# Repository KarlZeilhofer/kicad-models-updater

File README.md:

kicad-models-updater
====================
Reload the 3D Models in a .kicad_pcb File from the Libraries
------------------------------------------------------------

You would like to use this script, if you have modified many of the 3D models
in your footprint libraries. Another use could be to get a verbose
health report regarding footprints and it's libraries.

It takes a `.kicad_pcb` file, laods the used footprints from the
libraries and modifies the entries for a 3D model in the PCB file
without modifying any other fields. A diff will show only
the intended modifications (great for git).

## Usage
run `kicad-models-updater` in your KiCad project directory, and the
rest should be done by the script.

If you have multiple config paths on your system (e.g. KiCad 4/5 in
parallel), you have to specify
one of them with `-c CONFIGPATH`.

### Help
```
usage: kicad-models-updater [-h] [-c CPATH] [-p PPATH] [-f PCBFILE]
                            [-o OUTPUTFILE] [--dryrun] [--version]

Gets paths for 3D models from the used footrints and updates it in the
.kicad_pcb file without changing any other properties in the layout.

optional arguments:
  -h, --help            show this help message and exit
  -c CPATH, --configpath CPATH
                        system wide config path, where kicad_comman and fp-
                        lib-table can be found. Default is
                        /home/karl/.config/kicad
  -p PPATH, --projectpath PPATH
                        path to kicad project, where .kicad_pcb and optional
                        fp-lib-table can be found. Default is the current
                        working directory
  -f PCBFILE, --pcbfile PCBFILE
                        .kicad_pcb file to be modified. Default is the
                        .kicad_pcb in the project path. The --projectpath is
                        overridden by a given --pcbfile
  -o OUTPUTFILE, --output OUTPUTFILE
                        .kicad_pcb file to write the modified PCB file to.
                        Default is the input file, see --pcbfile Use this
                        option, if you do not want to overwrite the original
                        file
  --dryrun              run through all steps, except writing the output file
  --version             show program's version number and exit

GitHub: https://github.com/KarlZeilhofer/kicad-models-updater
```

## Details
The footprint libraries are discoverd like they are discovered by KiCad
itself using `kicad_common`, global `fp-lib-table` and projcet's
`fp-lib-table`.
This leads to a very smooth user experience and best possible
integrity of the modifications.

Various warnings are reported, if something isn't as expected:
* missing kicad_common
* missing fp-lib-table
* missing footprint library
* missing 3D model file
* multiple model entries in library or PCB footprint

## Installation
The file `kicad-models-updater.py` should be made executable. I added a
symlink to `/usr/bin/kicad-models-updater` on my Linux system, so I
can easily call it from any project directory.

## Status
* tested on linux with python 3.5.2

## Limitations
* only for KiCad 4 and newer with fp-lib-table and .pretty libs
* path substitutions are applied only once (`KicadCommon.py`)

## License
GPL V3, (c) Karl Zeilhofer, www.team14.at

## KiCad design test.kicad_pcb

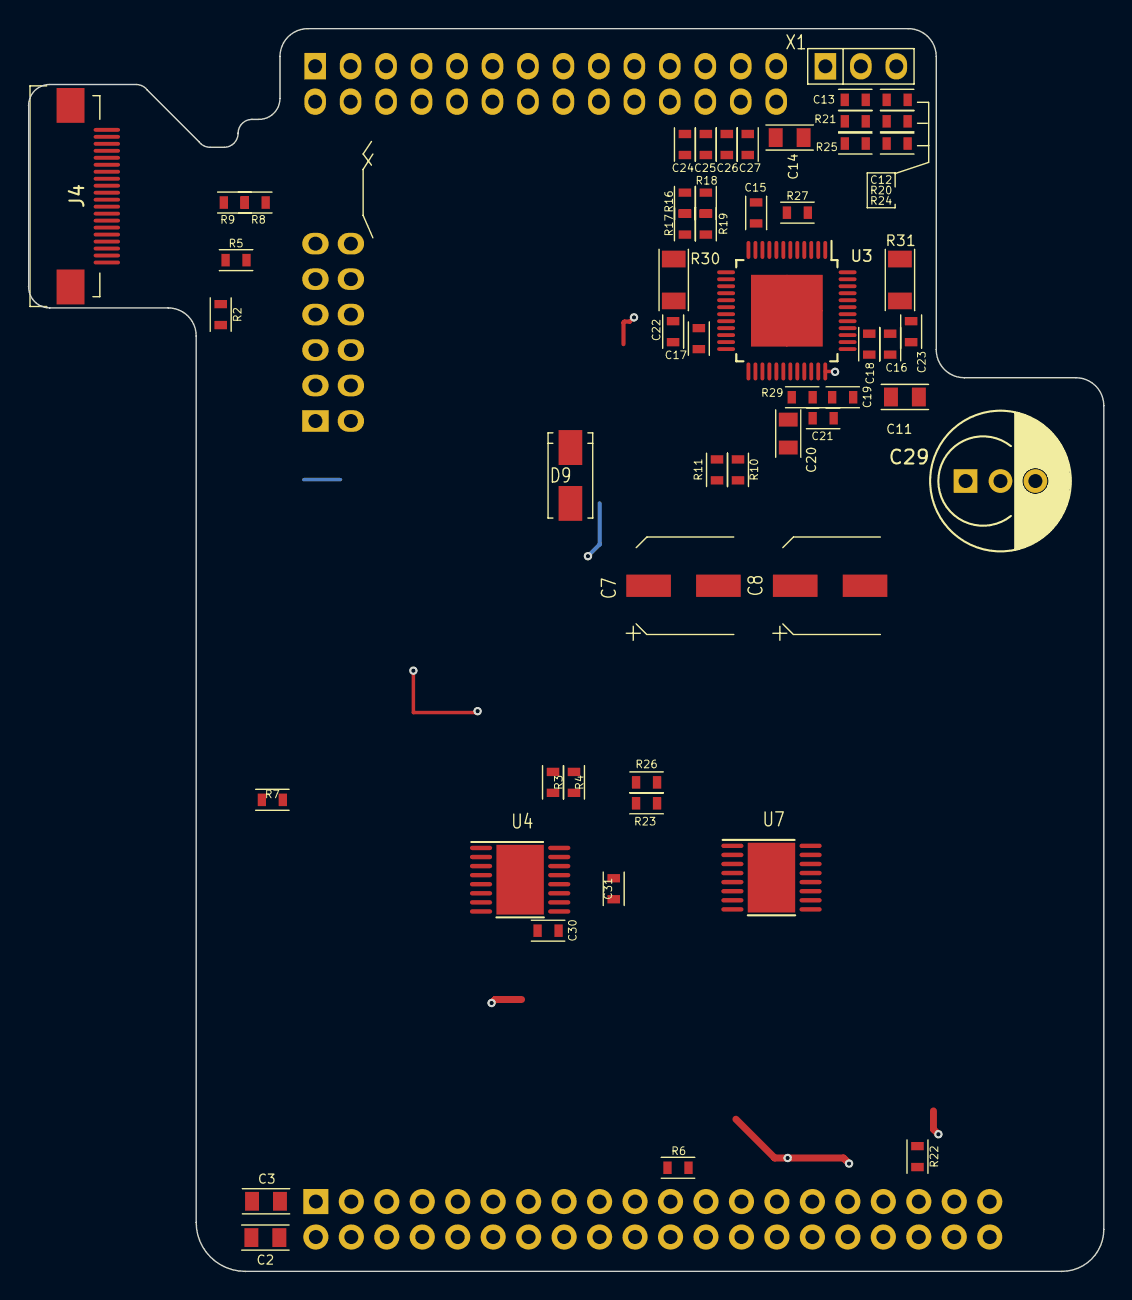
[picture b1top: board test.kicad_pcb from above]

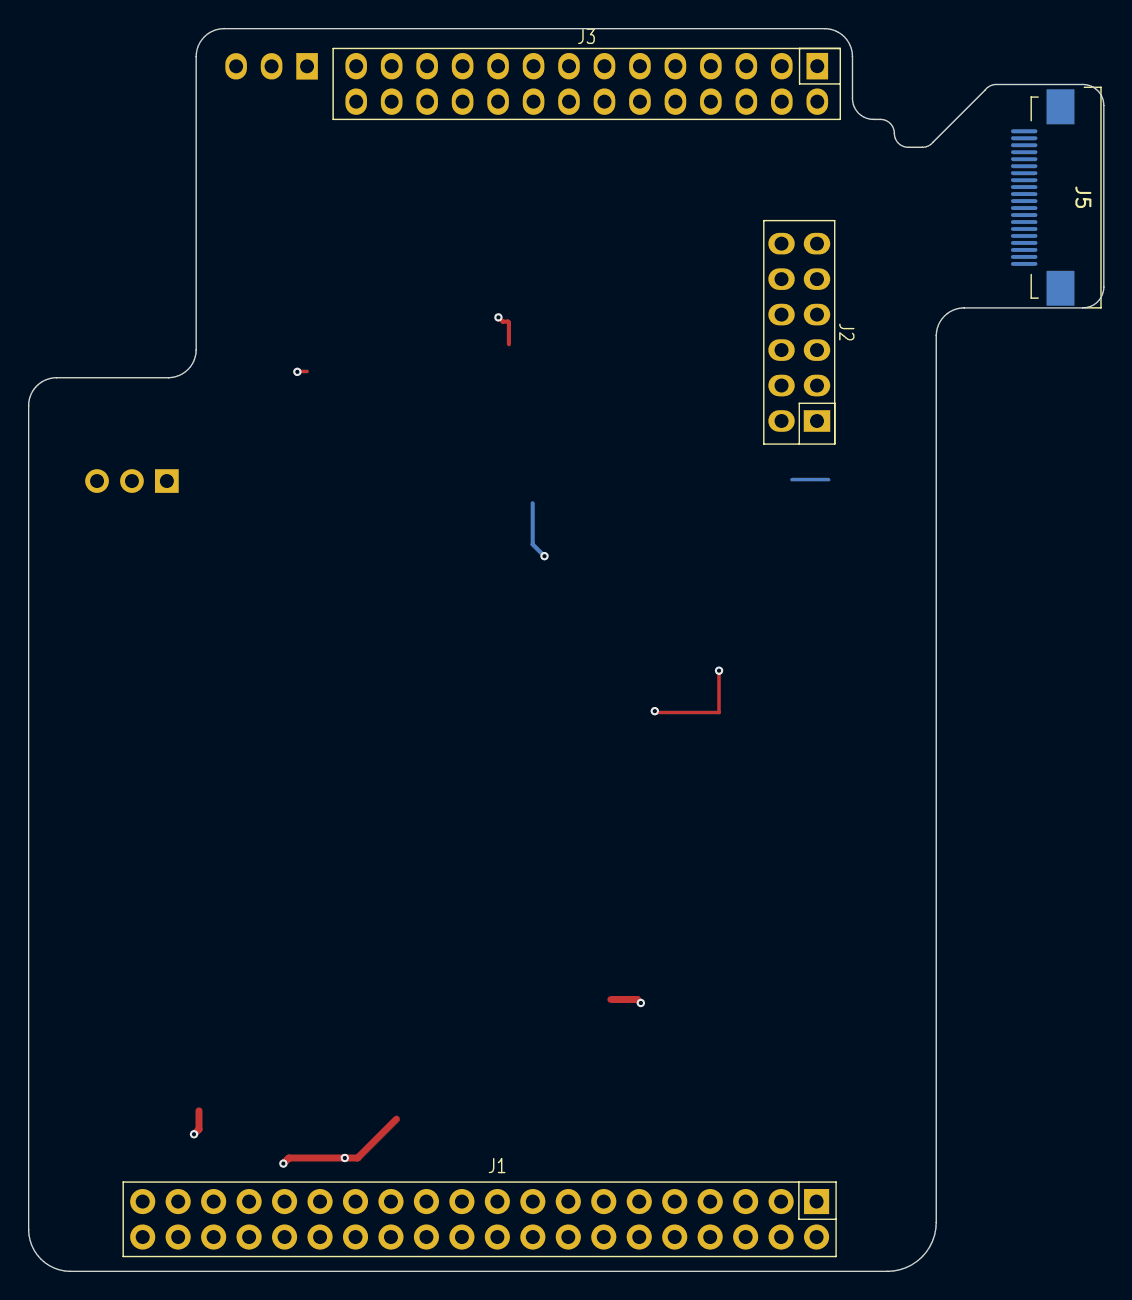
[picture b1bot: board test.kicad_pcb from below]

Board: 4 copper layers, 77.0 x 89.0 mm, 59 parts (4 on the bottom side), 45 nets.

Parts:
C2, C3: DNP; C2012m
C7, C8: C_pol; ELKO_D
C11, C14: 2u2/50V; C2012m
C12, C13: DNP; C1608m
C15, C18, C22, C23, C31: 100n; C1608m
C16, C17, C30: 100n/50V; C1608m
C19: 22n/50V; C1608m
C20: 4.7u; C2012m
C21: 470n; C1608m
C24, C25, C26, C27: 1n/ESD; C1608m
C29: C_pol; C_Radial_D10_D6.3
D9: SMAJ33CA; SMA
J1: Raspberry_Pi_2_3; Pin_Header_Straight_20x2_Female
J2: Buchse_02x06; Pin_Header_Straight_Female_2x6
J3: Buchse_02x14; Pin_Header_Straight_Female_2x14
J4, J5: ZIF0502DH; ZIF0520UH
R2, R3, R4, R5, R6, R7: 100R; R1608m
R8, R16, R19: 0R; R1608m
R9, R17, R18, R20, R21: DNP; R1608m
R10, R11, R22, R23, R26, R27: 470R; R1608m
R24, R25: 4k7; R1608m
R29: 3R3; R1608m
R30, R31: TBD; R3216m
U3: TMC5130-TA; TQFP-48-EP_7x7mm_Pitch0.5mm
U4, U7: DRV8816; HTSSOP-16_4.4x5mm_Pitch0.65mm_EP
X1: DNP; Pin_Header_Straight_1x3

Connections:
+3V3: C3.1, C15.1, J1.1, J1.17, J2.2, J4.1, J5.1, R9.1, R16.1, R18.1, R24.1, R25.1, U3.10
+5V: C2.1, J1.2, J1.4, J2.10, R8.1
/BLVDD: J4.17, J4.18, J5.17, J5.18, R8.2, R9.2
/CS_DISP_cab: J4.6, J5.6, R6.2
/GPIO34/VCP: C31.1, U4.14
/INT_DISP: J1.8, R2.1
/INT_DISP_cab: J4.7, J5.7, R2.2
/IO1: J3.10, U7.7
/IO2: J3.9, U7.10
/IO3: J3.8, U4.7
/IO4: J3.7, U4.10
/MISO: J1.21, R5.1, R27.1
/MISO_DISP: J4.4, J5.4, R5.2
/MOSI: J1.19, R4.1, R23.1
/MOSI_DISP: J4.5, J5.5, R4.2
/PD_DISP_cab: J4.8, J5.8, R7.2
/SCLK: J1.23, R3.1, R26.1
/SCLK_DISP: J4.3, J5.3, R3.2
/STP_A1: C26.2, J3.25, U3.46
/STP_A2: C27.1, J3.26, U3.42
/STP_B1: C24.2, J3.23, U3.15
/STP_B2: C25.1, J3.24, U3.19
/Stepperdriver/BRA: C23.1, R31.1, U3.44
/Stepperdriver/BRB: C22.1, R30.1, U3.17
/Stepperdriver/REFL_CON: C12.1, R20.2, X1.3
/Stepperdriver/REFR_CON: C13.1, R21.2, X1.2
/~CS_DISP: J1.24, R6.1
/~CS_Stepper: J1.35, R22.1
GND: C2.2, C3.2, C7.2, C8.2, C11.2, C12.2, C13.2, C14.2, C15.2, C16.2, C17.2, C20.1, C21.1, C22.2, C23.2, C24.1, C25.2, C26.1, C27.2, C29.2, C30.2, D9.2, J1.6, J1.9, J1.14, J1.20, J1.25, J1.30, J1.34, J1.39, J2.1, J2.9, J2.11, J3.1, J3.3, J3.5, J3.21, J3.27, J4.2, J4.19, J4.20, J4.21, J5.2, J5.19, J5.20, J5.21, R17.1, R19.1, R30.2, R31.2, U3.1, U3.2, U3.6, U3.13, U3.28, U3.31, U3.32, U3.36, U3.48, U3.49, U4.4, U4.13, U4.17, U7.4, U7.13, U7.17, X1.1
unnamed: C18.1, U3.38
unnamed: C19.1, U3.37
unnamed: C19.2, U3.35
unnamed: C20.2, R29.1, U3.33
unnamed: C21.2, R29.2, U3.34
unnamed: R10.2, U3.27
unnamed: R11.2, U3.26
unnamed: R16.2, R17.2, U3.12
unnamed: R18.2, R19.2, U3.11
unnamed: R20.1, R24.2, U3.8
unnamed: R21.1, R25.2, U3.9
unnamed: R22.2, U3.3
unnamed: R23.2, U3.5
unnamed: R26.2, U3.4
unnamed: R27.2, U3.7
VExt: C7.1, C8.1, C11.1, C14.1, C16.1, C17.1, C18.2, C29.1, C30.1, C31.2, J3.2, J3.22, J3.28, U3.21, U3.39, U3.40, U4.9, U7.9

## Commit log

2018-04-30 initial commit, WIP
2018-04-30 working demo
2018-04-30 everything parses fine...\nStill missing: \n* look for .kicad_mod files\n* parse them\n* modify the pcb file\n* save it
2018-04-30 ignore .idea
2018-04-30 add changelog
2018-05-01 ignore pycache
2018-05-01 WIP: parse and replace has been working...
    refactored classes (removed "variable declarations", moved them into the __init__
2018-05-01 works quite well, still some minor TODOs
2018-05-01 further improvements and bugfixes
2018-05-01 refactored into a App class, add output formating
    post commit
    update changelog
2018-05-01 major bugfix (escaped double quote), and others...
    update changelog
2018-05-01 release of v18.0.0
2018-05-05 release of V18.0.1

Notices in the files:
test.kicad_pcb:
Attribution 4.0 International (CC BY 4.0)
